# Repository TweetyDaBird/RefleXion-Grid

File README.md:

# RefleXion
 Ortho Split Keyboard

 -------------

This is a joint project with concept by 'The Reflex' (Pedro Quaresma), and design by 'TweetyDaBird' (Markus Knutsson).

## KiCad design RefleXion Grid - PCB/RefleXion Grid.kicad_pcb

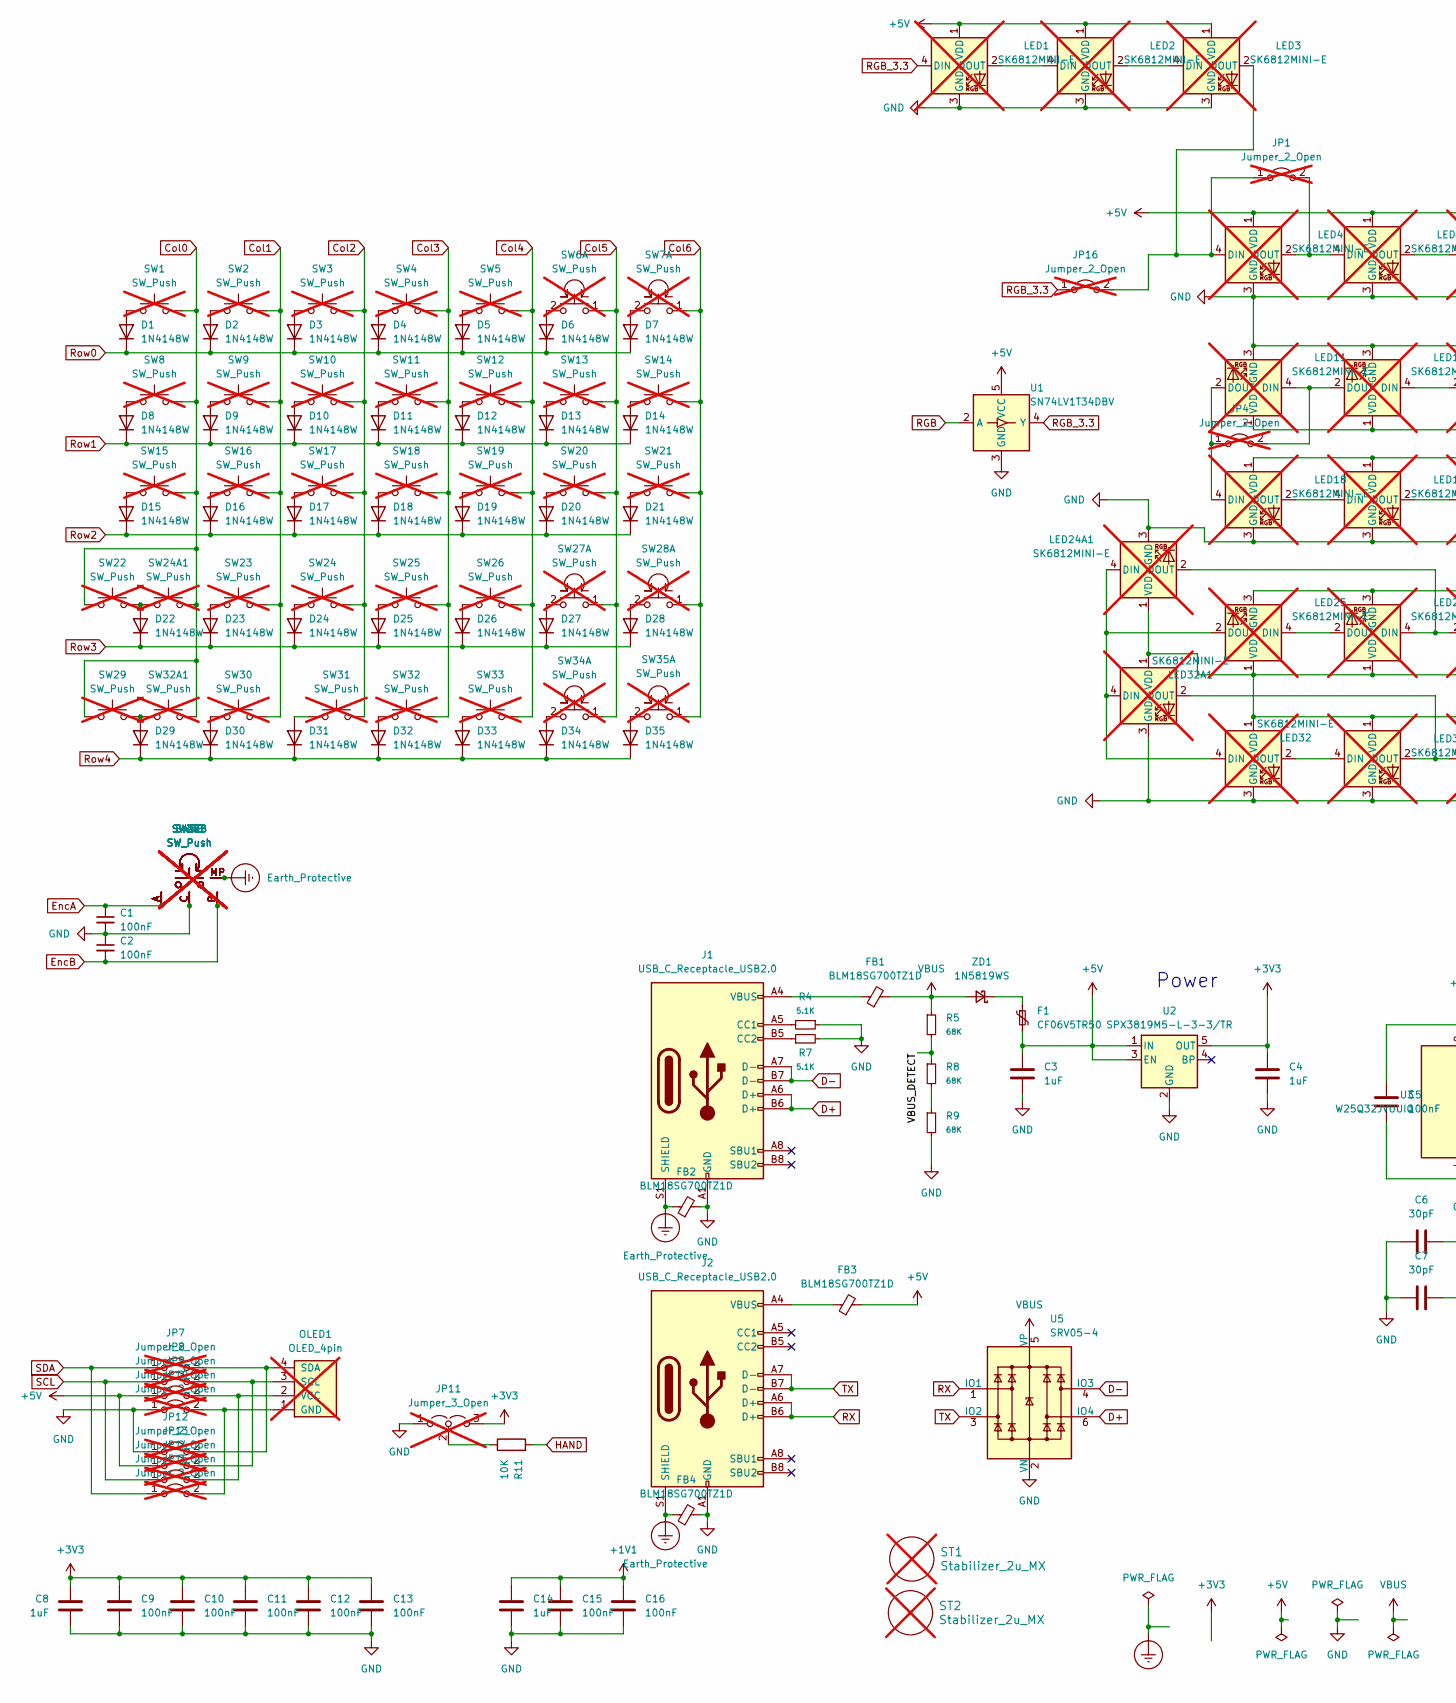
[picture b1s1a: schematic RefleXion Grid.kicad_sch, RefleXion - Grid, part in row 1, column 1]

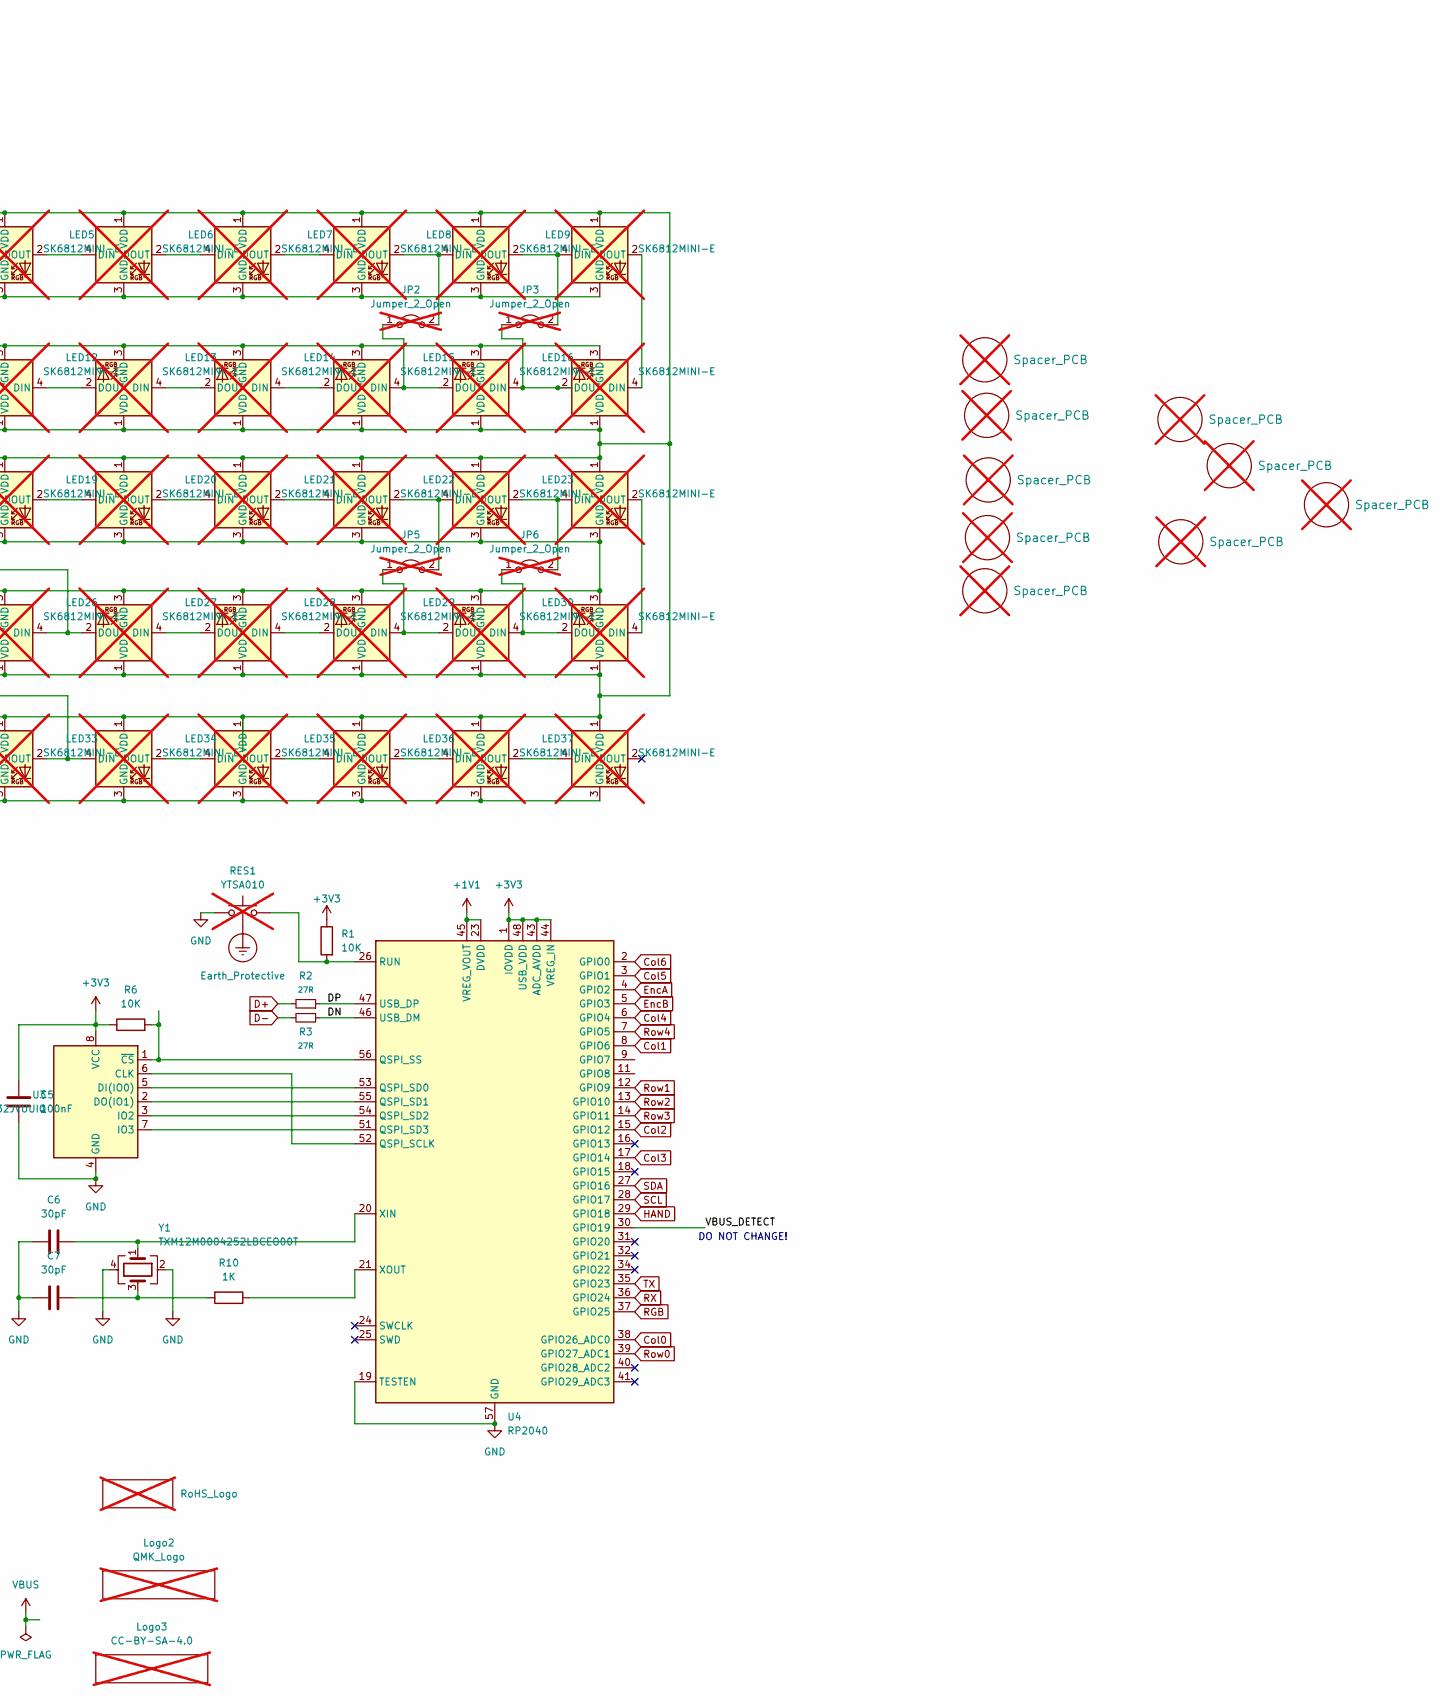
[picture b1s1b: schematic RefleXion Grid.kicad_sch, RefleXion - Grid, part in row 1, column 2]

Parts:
C1, C2, C5, C9, C10, C11, C12, C13, C15, C16: 100nF; C_0402_1005Metric; LCSC C513772
C3, C4, C8, C14: 1uF; C_0402_1005Metric
C6, C7: 30pF; C_0402_1005Metric
D1, D2, D3, D4, D5, D6, D7, D8, D9, D10, D11, D12, D13, D14, D15, D16, D17, D18, D19, D20, D21, D22, D23, D24, D25, D26, D27, D28, D29, D30, D31, D32, D33, D34, D35: 1N4148W; D_SOD-123
F1: CF06V5TR50; R_0603_1608Metric; LCSC C163116
FB1, FB2, FB3, FB4: BLM18SG700TZ1D; C_0603_1608Metric_Pad1.08x0.95mm_HandSolder; LCSC C882974
H1, H2, H3, H4, H5, H6, H7, H8, H9: Spacer_PCB; Spacer PCB hole; not fitted
J1: USB_C_Receptacle_USB2.0; HRO_TYPE-C-31-M-12_double_sided; LCSC C165948
J2: USB_C_Receptacle_USB2.0; HRO_TYPE-C-31-M-12_double_sided_serial link; LCSC C165948
JP1, JP2, JP3, JP4, JP5, JP6, JP7, JP8, JP9, JP10, JP12, JP13, JP14, JP15, JP16: Jumper_2_Open; Jumper_min_v2; not fitted
JP11: Jumper_3_Open; SolderJumper-3_open_mini; not fitted
LED1, LED2, LED3, LED4, LED5, LED6, LED7, LED8, LED9, LED10, LED11, LED12, LED13, LED14, LED15, LED16, LED17, LED18, LED19, LED20, LED21, LED22, LED23, LED24, LED24A1, LED25, LED26, LED27, LED28, LED29, LED30, LED31, LED32, LED32A1, LED33, LED34, LED35, LED36, LED37, LED38: SK6812MINI-E; MX_SK6812MINI-E_REVERSIBLE_SMALL_PAD; not fitted
Logo1: RoHS_Logo; RoHs; not fitted
Logo2: QMK_Logo; Powered_by_QMK; not fitted
Logo3: CC-BY-SA-4.0; CC_BY_SA_40_line; not fitted
OLED1: OLED_4pin; OLED_SSD1306_128x32_0_91_inch; not fitted
R1, R6, R11: 10K; R_0402_1005Metric; LCSC C2078429
R2, R3: 27R; R_0402_1005Metric; LCSC C1701143
R4, R7: 5.1K; R_0402_1005Metric; LCSC C2075916
R5, R8, R9: 68K; R_0402_1005Metric; LCSC C2075916
R10: 1K; R_0402_1005Metric; LCSC C2139907
RES1: YTSA010; YTS-A002 Double-sided; LCSC C2888934; not fitted
ST1, ST2: Stabilizer_2u_MX; Stabilizer_Cherry_MX_2.00u; not fitted
SW1, SW2, SW3, SW4, SW5, SW8, SW9, SW10, SW11, SW12, SW13, SW14, SW15, SW16, SW17, SW18, SW19, SW20, SW21, SW22, SW23, SW24, SW24A1, SW25, SW26, SW29, SW30, SW31, SW32, SW32A1, SW33: SW_Push; SW_MX_HotSwap_Reversible; not fitted
SW6, SW7, SW27, SW28, SW34, SW35: SW_Push; SW_MX_HotSwap_Reversible_Encoder; not fitted
U1: SN74LV1T34DBV; SOT-23-5; LCSC C100024
U2: SPX3819M5-L-3-3/TR; SOT-23-5; LCSC C9055
U3: W25Q32JVUUIQ; USON-8_4x3mm_P0.8mm; LCSC C2999380
U4: RP2040; QFN-56-1EP_7x7mm_P0.4mm_EP3.2x3.2mm_ThermalVias; LCSC C2040
U5: SRV05-4; SOT-23-6; LCSC C558418
Y1: TXM12M0004252LBCEO00T; Crystal_SMD_2520-4Pin_2.5x2.0mm; PartNo C284156; LCSC C284156
ZD1: 1N5819WS; D_SOD-323F

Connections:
+1V1: C14.1, C15.1, C16.1, U4.23 (DVDD), U4.45 (VREG_VOUT), U4.50 (DVDD)
+3V3: C4.1, C5.1, C8.1, C9.1, C10.1, C11.1, C12.1, C13.1, JP11.3 (B), R1.1, R6.1, U2.5 (OUT), U3.8 (VCC), U4.1 (IOVDD), U4.10 (IOVDD), U4.22 (IOVDD), U4.33 (IOVDD), U4.42 (IOVDD), U4.43 (ADC_AVDD), U4.44 (VREG_IN), U4.48 (USB_VDD), U4.49 (IOVDD)
+5V: C3.1, F1.2, FB3.2, JP9.1 (A), JP13.1 (A), LED1.1 (VDD), LED2.1 (VDD), LED3.1 (VDD), LED4.1 (VDD), LED5.1 (VDD), LED6.1 (VDD), LED7.1 (VDD), LED8.1 (VDD), LED9.1 (VDD), LED10.1 (VDD), LED11.1 (VDD), LED12.1 (VDD), LED13.1 (VDD), LED14.1 (VDD), LED15.1 (VDD), LED16.1 (VDD), LED17.1 (VDD), LED18.1 (VDD), LED19.1 (VDD), LED20.1 (VDD), LED21.1 (VDD), LED22.1 (VDD), LED23.1 (VDD), LED24.1 (VDD), LED24A1.1 (VDD), LED25.1 (VDD), LED26.1 (VDD), LED27.1 (VDD), LED28.1 (VDD), LED29.1 (VDD), LED30.1 (VDD), LED31.1 (VDD), LED32.1 (VDD), LED32A1.1 (VDD), LED33.1 (VDD), LED34.1 (VDD), LED35.1 (VDD), LED36.1 (VDD), LED37.1 (VDD), LED38.1 (VDD), U1.5 (VCC), U2.1 (IN), U2.3 (EN)
/DN: R3.1, U4.46 (USB_DM)
/DP: R2.1, U4.47 (USB_DP)
/VBUS_DETECT: R5.2, R8.1, U4.30 (GPIO19)
Col0: SW1.1, SW8.1, SW15.1, SW22.1, SW24A1.1, SW29.1, SW32A1.1, U4.38 (GPIO26_ADC0)
Col1: SW2.2, SW9.2, SW16.2, SW23.2, SW30.2, U4.8 (GPIO6)
Col2: SW3.2, SW10.2, SW17.2, SW24.2, SW31.2, U4.15 (GPIO12)
Col3: SW4.2, SW11.2, SW18.2, SW25.2, SW32.2, U4.17 (GPIO14)
Col4: SW5.2, SW12.2, SW19.2, SW26.2, SW33.2, U4.6 (GPIO4)
Col5: SW6.1, SW13.1, SW20.1, SW27.1, SW34.1, U4.3 (GPIO1)
Col6: SW7.1, SW14.1, SW21.1, SW28.1, SW35.1, U4.2 (GPIO0)
D+: J1.A6 (D+), J1.B6 (D+), R2.2, U5.6 (IO4)
D-: J1.A7 (D-), J1.B7 (D-), R3.2, U5.4 (IO3)
Earth_Protective: FB2.1, FB4.1, J1.S1 (SHIELD), J2.S1 (SHIELD), RES1.3, SW6.MP, SW7.MP, SW27.MP, SW28.MP, SW34.MP, SW35.MP
EncA: C1.1, SW6.A, SW7.A, SW27.A, SW28.A, SW34.A, SW35.A, U4.4 (GPIO2)
EncB: C2.2, SW6.B, SW7.B, SW27.B, SW28.B, SW34.B, SW35.B, U4.5 (GPIO3)
GND: C1.2, C2.1, C3.2, C4.2, C5.2, C6.2, C7.2, C8.2, C9.2, C10.2, C11.2, C12.2, C13.2, C14.2, C15.2, C16.2, FB2.2, FB4.2, J1.A1 (GND), J1.A12 (GND), J1.B1 (GND), J1.B12 (GND), J2.A1 (GND), J2.A12 (GND), J2.B1 (GND), J2.B12 (GND), JP10.1 (A), JP11.1 (A), JP12.1 (A), LED1.3 (GND), LED2.3 (GND), LED3.3 (GND), LED4.3 (GND), LED5.3 (GND), LED6.3 (GND), LED7.3 (GND), LED8.3 (GND), LED9.3 (GND), LED10.3 (GND), LED11.3 (GND), LED12.3 (GND), LED13.3 (GND), LED14.3 (GND), LED15.3 (GND), LED16.3 (GND), LED17.3 (GND), LED18.3 (GND), LED19.3 (GND), LED20.3 (GND), LED21.3 (GND), LED22.3 (GND), LED23.3 (GND), LED24.3 (GND), LED24A1.3 (GND), LED25.3 (GND), LED26.3 (GND), LED27.3 (GND), LED28.3 (GND), LED29.3 (GND), LED30.3 (GND), LED31.3 (GND), LED32.3 (GND), LED32A1.3 (GND), LED33.3 (GND), LED34.3 (GND), LED35.3 (GND), LED36.3 (GND), LED37.3 (GND), LED38.3 (GND), R4.1, R7.2, R9.2, RES1.1, SW6.C, SW7.C, SW27.C, SW28.C, SW34.C, SW35.C, U1.3 (GND), U2.2 (GND), U3.4 (GND), U4.19 (TESTEN), U4.57 (GND), U5.2 (VN), Y1.2, Y1.4
HAND: R11.2, U4.29 (GPIO18)
unnamed: C7.1, R10.2, Y1.3
unnamed: D1.2 (A), SW1.2
unnamed: D2.2 (A), SW2.1
unnamed: D3.2 (A), SW3.1
unnamed: D4.2 (A), SW4.1
unnamed: D5.2 (A), SW5.1
unnamed: D6.2 (A), SW6.2
unnamed: D7.2 (A), SW7.2
unnamed: D8.2 (A), SW8.2
unnamed: D9.2 (A), SW9.1
unnamed: D10.2 (A), SW10.1
unnamed: D11.2 (A), SW11.1
unnamed: D12.2 (A), SW12.1
unnamed: D13.2 (A), SW13.2
unnamed: D14.2 (A), SW14.2
unnamed: D15.2 (A), SW15.2
unnamed: D16.2 (A), SW16.1
unnamed: D17.2 (A), SW17.1
unnamed: D18.2 (A), SW18.1
unnamed: D19.2 (A), SW19.1
unnamed: D20.2 (A), SW20.2
unnamed: D21.2 (A), SW21.2
unnamed: D22.2 (A), SW22.2, SW24A1.2
unnamed: D23.2 (A), SW23.1
unnamed: D24.2 (A), SW24.1
unnamed: D25.2 (A), SW25.1
unnamed: D26.2 (A), SW26.1
unnamed: D27.2 (A), SW27.2
unnamed: D28.2 (A), SW28.2
unnamed: D29.2 (A), SW29.2, SW32A1.2
unnamed: D30.2 (A), SW30.1
unnamed: D31.2 (A), SW31.1
unnamed: D32.2 (A), SW32.1
unnamed: D33.2 (A), SW33.1
unnamed: D34.2 (A), SW34.2
unnamed: D35.2 (A), SW35.2
unnamed: FB1.1, J1.A4 (VBUS), J1.A9 (VBUS), J1.B4 (VBUS), J1.B9 (VBUS)
unnamed: FB3.1, J2.A4 (VBUS), J2.A9 (VBUS), J2.B4 (VBUS), J2.B9 (VBUS)
unnamed: J1.A5 (CC1), R4.2
unnamed: J1.B5 (CC2), R7.1
unnamed: JP1.1 (A), JP16.2 (B), LED3.2 (DOUT), LED4.4 (DIN)
unnamed: JP1.2 (B), LED4.2 (DOUT), LED5.4 (DIN)
unnamed: JP2.1 (A), LED15.4 (DIN), LED16.2 (DOUT)
unnamed: JP2.2 (B), LED8.2 (DOUT), LED9.4 (DIN)
unnamed: JP3.1 (A), LED16.4 (DIN), LED17.2 (DOUT)
unnamed: JP3.2 (B), LED9.2 (DOUT), LED10.4 (DIN)
unnamed: JP4.1 (A), LED11.2 (DOUT), LED18.4 (DIN)
unnamed: JP4.2 (B), LED11.4 (DIN), LED12.2 (DOUT)
unnamed: JP5.1 (A), LED29.4 (DIN), LED30.2 (DOUT)
unnamed: JP5.2 (B), LED22.2 (DOUT), LED23.4 (DIN)
unnamed: JP6.1 (A), LED30.4 (DIN), LED31.2 (DOUT)
unnamed: JP6.2 (B), LED23.2 (DOUT), LED24.4 (DIN)
unnamed: JP10.2 (B), JP15.2 (B), OLED1.1 (GND)
unnamed: JP11.2 (C), R11.1
unnamed: JP7.2 (B), JP12.2 (B), OLED1.4 (SDA)
unnamed: JP8.2 (B), JP13.2 (B), OLED1.3 (SCL)
unnamed: JP9.2 (B), JP14.2 (B), OLED1.2 (VCC)
unnamed: LED1.2 (DOUT), LED2.4 (DIN)
unnamed: LED2.2 (DOUT), LED3.4 (DIN)
unnamed: LED5.2 (DOUT), LED6.4 (DIN)
unnamed: LED6.2 (DOUT), LED7.4 (DIN)
unnamed: LED7.2 (DOUT), LED8.4 (DIN)
unnamed: LED10.2 (DOUT), LED17.4 (DIN)
unnamed: LED12.4 (DIN), LED13.2 (DOUT)
unnamed: LED13.4 (DIN), LED14.2 (DOUT)
unnamed: LED14.4 (DIN), LED15.2 (DOUT)
unnamed: LED18.2 (DOUT), LED19.4 (DIN)
unnamed: LED19.2 (DOUT), LED20.4 (DIN)
unnamed: LED20.2 (DOUT), LED21.4 (DIN)
unnamed: LED21.2 (DOUT), LED22.4 (DIN)
unnamed: LED24.2 (DOUT), LED31.4 (DIN)
unnamed: LED24A1.4 (DIN), LED25.2 (DOUT), LED32.4 (DIN), LED32A1.4 (DIN)
unnamed: LED24A1.2 (DOUT), LED26.4 (DIN), LED27.2 (DOUT)
unnamed: LED25.4 (DIN), LED26.2 (DOUT)
unnamed: LED27.4 (DIN), LED28.2 (DOUT)
unnamed: LED28.4 (DIN), LED29.2 (DOUT)
unnamed: LED32.2 (DOUT), LED33.4 (DIN)
unnamed: LED32A1.2 (DOUT), LED33.2 (DOUT), LED34.4 (DIN)
unnamed: LED34.2 (DOUT), LED35.4 (DIN)
unnamed: LED35.2 (DOUT), LED36.4 (DIN)
unnamed: LED36.2 (DOUT), LED37.4 (DIN)
unnamed: LED37.2 (DOUT), LED38.4 (DIN)
unnamed: R8.2, R9.1
unnamed: U3.6 (CLK), U4.52 (QSPI_SCLK)
unnamed: U3.5 (DI(IO0)), U4.53 (QSPI_SD0)
unnamed: U3.2 (DO(IO1)), U4.55 (QSPI_SD1)
unnamed: U3.3 (IO2), U4.54 (QSPI_SD2)
unnamed: U3.7 (IO3), U4.51 (QSPI_SD3)
unnamed: R6.2, U3.1 (~CS), U4.56 (QSPI_SS)
unnamed: R1.2, RES1.2, U4.26 (RUN)
unnamed: C6.1, U4.20 (XIN), Y1.1
unnamed: R10.1, U4.21 (XOUT)
unnamed: F1.1, ZD1.1 (K)
RGB: U1.2 (A), U4.37 (GPIO25)
RGB_3.3: JP16.1 (A), LED1.4 (DIN), U1.4 (Y)
RX: J2.A6 (D+), J2.B6 (D+), U4.36 (GPIO24), U5.1 (IO1)
Row0: D1.1 (K), D2.1 (K), D3.1 (K), D4.1 (K), D5.1 (K), D6.1 (K), D7.1 (K), U4.39 (GPIO27_ADC1)
Row1: D8.1 (K), D9.1 (K), D10.1 (K), D11.1 (K), D12.1 (K), D13.1 (K), D14.1 (K), U4.12 (GPIO9)
Row2: D15.1 (K), D16.1 (K), D17.1 (K), D18.1 (K), D19.1 (K), D20.1 (K), D21.1 (K), U4.13 (GPIO10)
Row3: D22.1 (K), D23.1 (K), D24.1 (K), D25.1 (K), D26.1 (K), D27.1 (K), D28.1 (K), U4.14 (GPIO11)
Row4: D29.1 (K), D30.1 (K), D31.1 (K), D32.1 (K), D33.1 (K), D34.1 (K), D35.1 (K), U4.7 (GPIO5)
SCL: JP8.1 (A), JP14.1 (A), U4.28 (GPIO17)
SDA: JP7.1 (A), JP15.1 (A), U4.27 (GPIO16)
TX: J2.A7 (D-), J2.B7 (D-), U4.35 (GPIO23), U5.3 (IO2)
VBUS: FB1.2, R5.1, U5.5 (VP), ZD1.2 (A)

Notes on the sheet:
Power
DO NOT CHANGE!

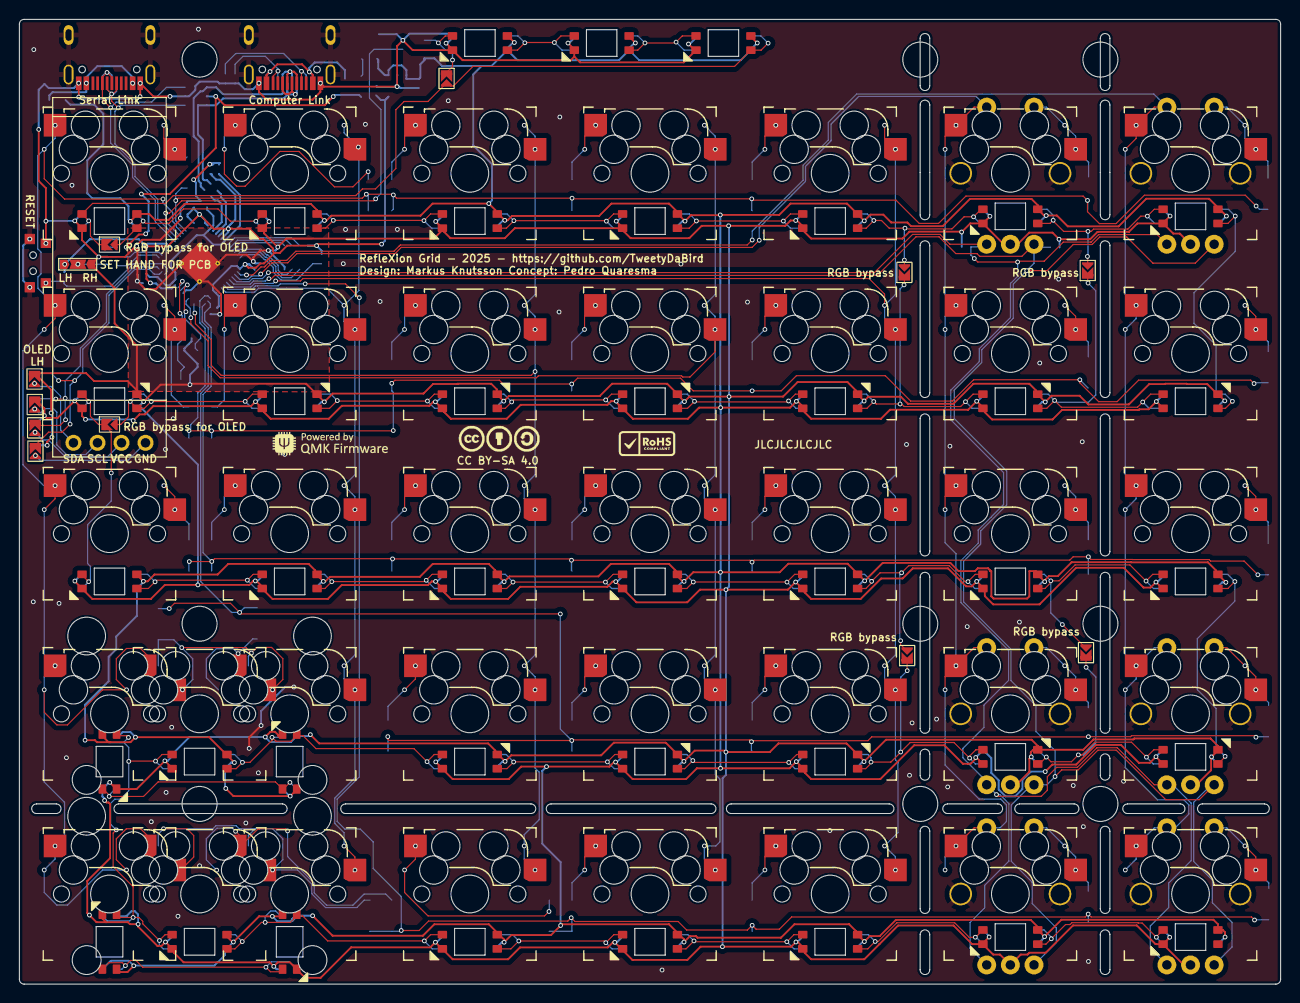
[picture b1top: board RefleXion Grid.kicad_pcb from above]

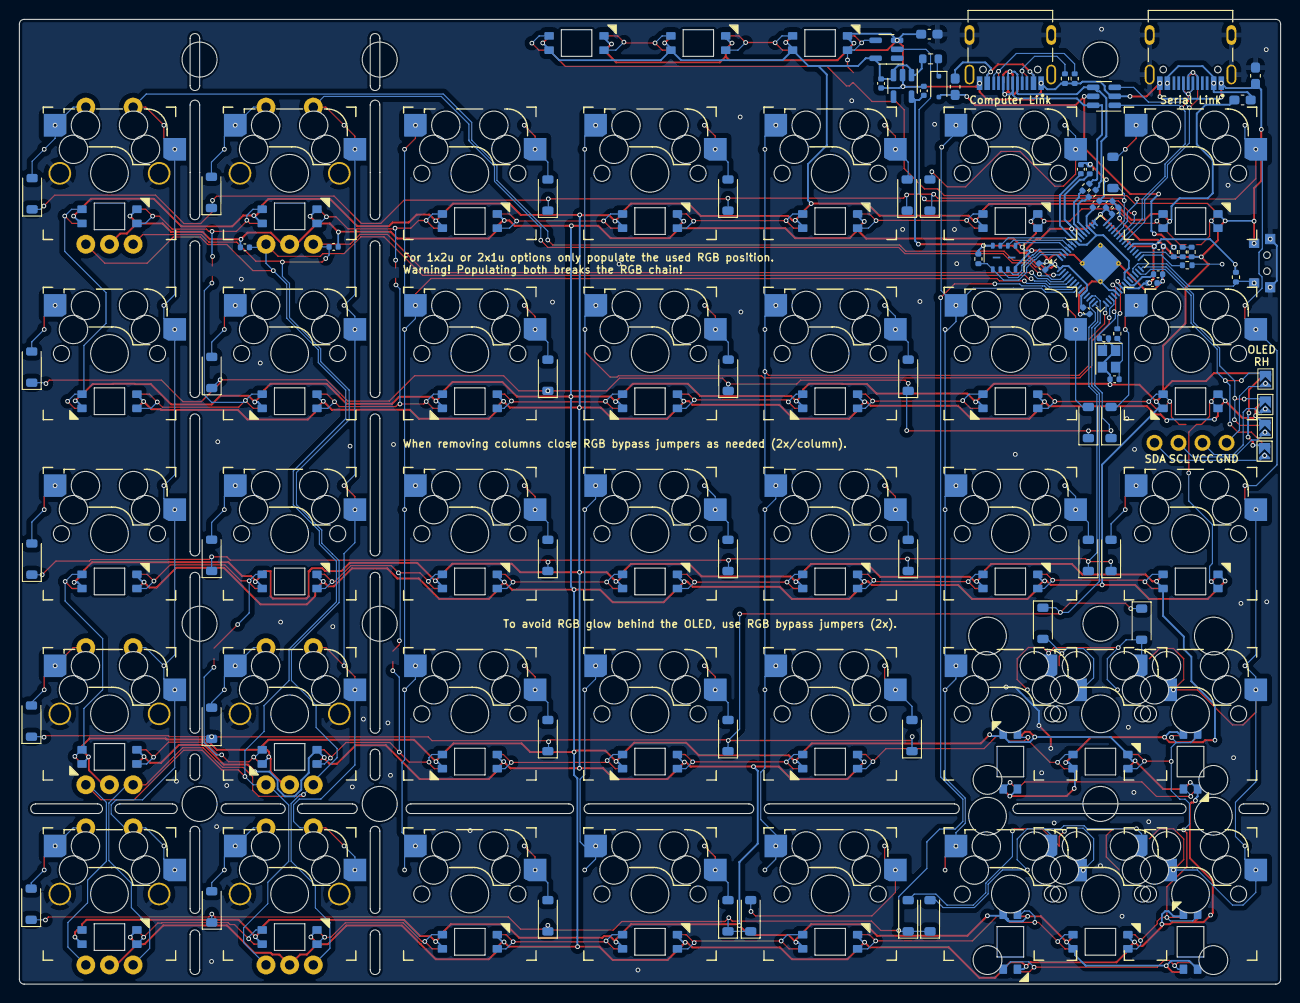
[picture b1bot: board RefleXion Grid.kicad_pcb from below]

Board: 2 copper layers, 133.4 x 102.0 mm, 185 parts (82 on the bottom side), 125 nets.

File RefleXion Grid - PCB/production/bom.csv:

Designator,Footprint,Quantity,Value,LCSC Part #
"C1, C10, C11, C12, C13, C15, C16, C2, C5, C9",0402,10,100nF,C513772
"C14, C3, C4, C8",0402,4,1uF,
"C6, C7",0402,2,30pF,
"D1, D10, D11, D12, D13, D14, D15, D16, D17, D18, D19, D2, D20, D21, D22, D23, D24, D25, D26, D27, D28, D29, D3, D30, D31, D32, D33, D34, D35, D4, D5, D6, D7, D8, D9",D_SOD-123,35,1N4148W,
F1,0603,1,CF06V5TR50,C163116
"FB1, FB2, FB3, FB4",0603,4,BLM18SG700TZ1D,C882974
"J1, J2",HRO-TYPE-C-31-M-13x,2,USB_C_Receptacle_USB2.0,C165948
"R1, R11, R6",0402,3,10K,C2078429
R10,0402,1,1K,C2139907
"R2, R3",0402,2,27R,C1701143
"R4, R7",0402,2,5.1K,C2075916
"R5, R8, R9",0402,3,68K,C2075916
U1,SOT-23-5,1,SN74LV1T34DBV,C100024
U2,SOT-23-5,1,SPX3819M5-L-3-3/TR,C9055
U3,USON-8_4x3mm_P0.8mm,1,W25Q32JVUUIQ,C2999380
U4,QFN-56-1EP_7x7mm_P0.4mm_EP3.2x3.2mm_ThermalVias,1,RP2040,C2040
U5,SOT-23-6,1,SRV05-4,C558418
Y1,Crystal_SMD_2520-4Pin_2.5x2.0mm,1,TXM12M0004252LBCEO00T,C284156
ZD1,D_SOD-323F,1,1N5819WS,

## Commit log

2026-01-15 Initial Commit
    # Conflicts:
    # .gitignore

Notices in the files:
RefleXion Grid - PCB/RefleXion Grid.kicad_pcb:
Licensed under Creative Commons BY-SA 4.0 International
